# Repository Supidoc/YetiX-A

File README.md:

# YetiX-A

Small development board for the NXP MCX-A series MCUs.

YetiX-A is designed to be compact while still exposing most peripherals needed for firmware development, board bring-up, and protocol testing.

## Features

- SPI EEPROM
- SPI micro SD card slot
- CAN transceiver with optional bus termination
- USB-C connector with ISP button support
- 42 board pins exposing almost all MCU peripherals
- 10-pin ARM Cortex debug connector

## Pin Out

Most MCU pins are routed directly to board pins.

Some signals (for example SPI1 MISO, MOSI, and SCK) are internally connected to onboard peripherals and are still exposed as board pins. Other signals (for example debug pins and chip select lines) are only internally connected and not exposed.

For the exact mapping of MCU pins to board pins, see:

- [assets/PIN_Functions.csv](assets/PIN_Functions.csv)

## Quick Start

1. Power the board via the USB-C receptecal or the 5V Pin
2. Connect a debugger to the 10-pin Cortex debug header, or use ISP mode over USB.
3. Flash a minimal firmware project (for example, a GPIO blink) to verify toolchain and board bring-up.

## Programming And Debug

### SWD/JTAG Debug Header

YetiX-A includes a 10-pin ARM Cortex debug connector for standard MCU debugging workflows.

Recommended usage:

1. Power the board from USB-C or the intended external source.
2. Connect your debug probe to the Cortex header.
3. Use your preferred IDE/debug server to connect and flash.

### USB ISP Mode

The board supports ISP using the USB-C interface.

Typical flow:

1. Hold the ISP button.
2. Connect USB or reset the target if already connected.
3. Release the button.
4. Drag and drop the .uf2 file to the mass storage device.

## Onboard Peripherals

### SPI EEPROM (ST M95256-DF)

- Intended for non-volatile parameter/configuration storage.
- Shares SPI1 bus with SD-card and other externally connected devices.

### SPI micro SD Slot

- Intended for logging, file storage, or data exchange.
- Shares SPI1 bus with EEPROM and other externally connected devices.
- Switch to detect card insertion.

### CAN Transceiver (NXP TJA1042BT)

- 5V CAN Transceiver
- Optional footprints for termination.

## Documentation And Design Files

### KiCad Source

- Schematic: [YetiX-A_DevBoard.kicad_sch](YetiX-A_DevBoard.kicad_sch)
- PCB: [YetiX-A_DevBoard.kicad_pcb](YetiX-A_DevBoard.kicad_pcb)
- Project: [YetiX-A_DevBoard.kicad_pro](YetiX-A_DevBoard.kicad_pro)

### Exported Documentation

- Schematic PDF: [FabData/YetiX-A_Schematic.pdf](FabData/YetiX-A_Schematic.pdf)
- PCB layout PDF: [FabData/YetiX-A_PCB_Layout.pdf](FabData/YetiX-A_PCB_Layout.pdf)

### Manufacturing Outputs

All Documents for fabrication can be found in [FabData](FabData)

## Hardware Revisions

| Revision | Date | Notes |
| --- | --- | --- |
| 0.0.1 | - | Initial production package |
| 0.0.2 | - | Added optional CAN Termination |

## License

See [LICENSE](LICENSE).

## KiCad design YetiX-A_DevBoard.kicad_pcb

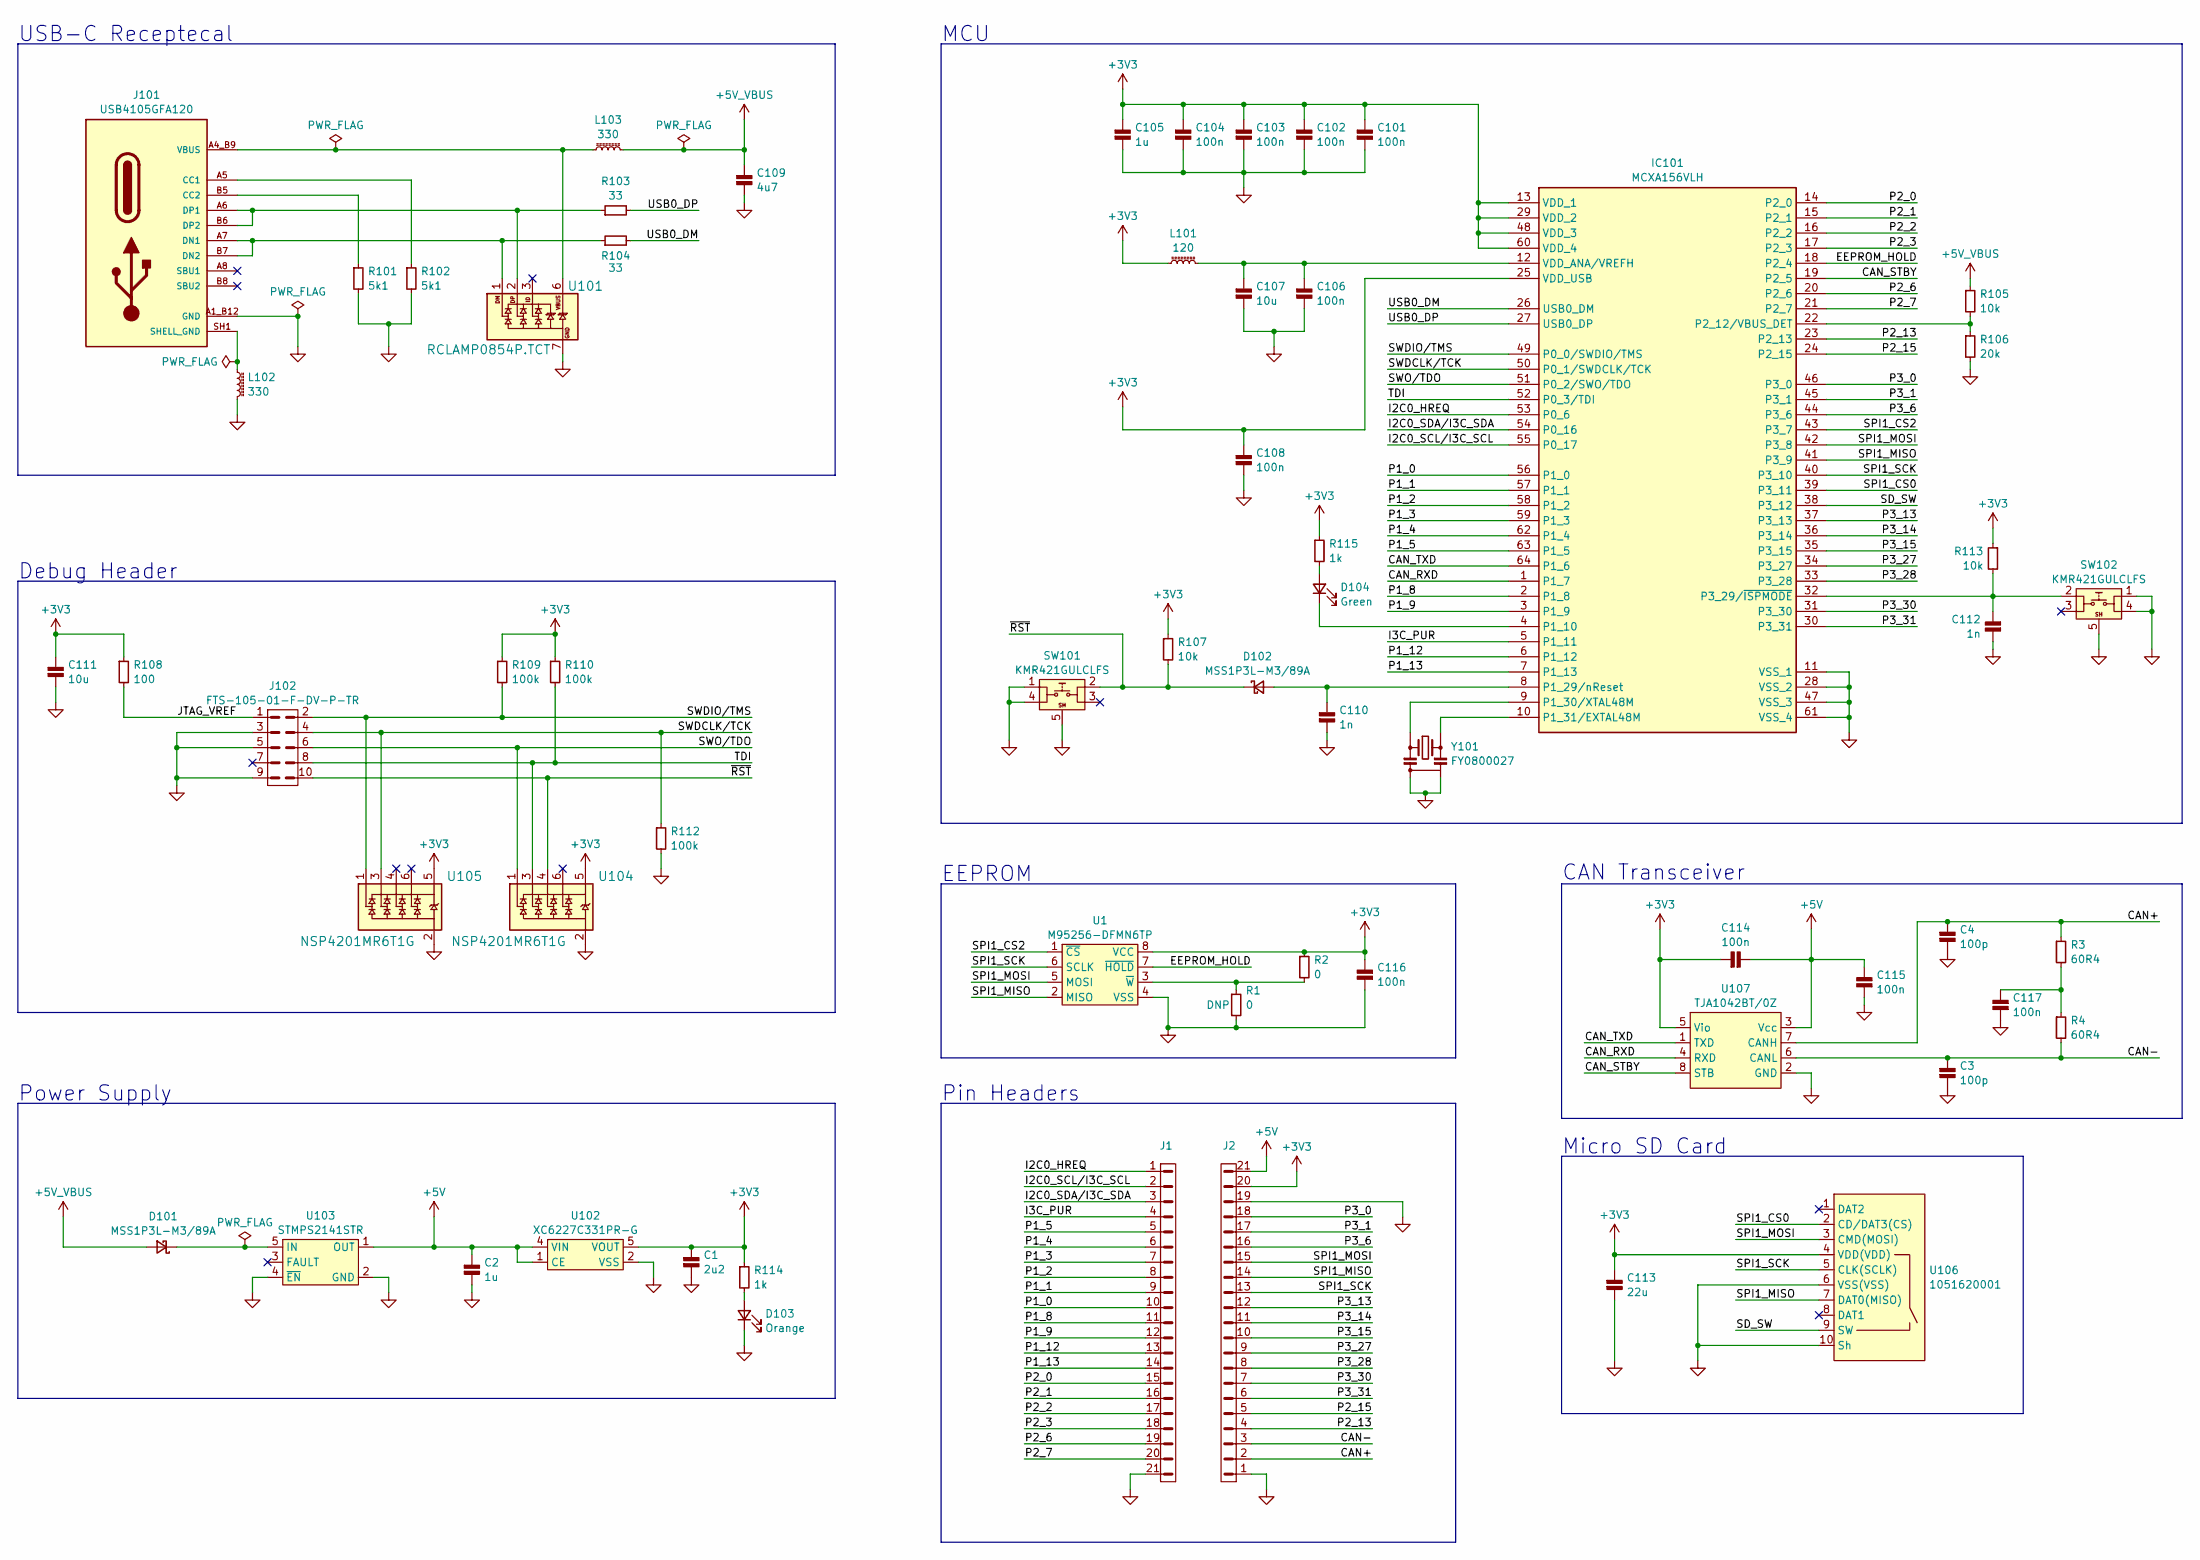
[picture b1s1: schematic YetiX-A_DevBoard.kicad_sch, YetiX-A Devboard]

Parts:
C1: 2u2; C_0603; Rating 10V 20%; MFR# CC0603KRX7R6BB225
C2, C105: 1u; C_0603; Rating 16V 10%; MFR# CC0603KRX7R7BB105
C3, C4: 100p; C_0603; Rating 100V 10%; MFR# CC0603KRX7R0BB101
C101, C102, C103, C104, C106, C108, C114, C115, C116, C117: 100n; C_0603; Rating 16V 10%; MFR# CC0603KRX7R7BB104
C107, C111: 10u; C_0603; Rating 10V 20%; MFR# CC0603MRX5R6BB106
C109: 4u7; C_0603; Rating 16V 10%; MFR# CC0603KRX5R7BB475
C110, C112: 1n; C_0603; Rating 50V 10%; MFR# CC0603KRX7R9BB103
C113: 22u; C_1206; Rating 10V 10%; MFR# CC1206KKX5R6BB226
D101, D102: MSS1P3L-M3/89A; DIODE_MSMP; Rating 30V 1A; MFR# MSS1P3L-M3/89A
D103: Orange; D_0603; Rating 2v 20mA 605nm; MFR# LTST-C190KFKT
D104: Green; D_0603; Rating 2v1 20mA 569nm; MFR# LTST-C190GKT
IC101: MCXA156VLH; QFP50P1200X1200X160-64N; MFR# MCXA156VLH
J1, J2: CONN HEADER VERT 22POS 2.54MM; PinHeader_1x21_P2.54mm_Vertical; MFR# 61302211121
J101: USB4105GFA120; GCT_USB4105GFA120; Rating 16 Pin; MFR# USB4105-GF-A-120
J102: FTS-105-01-F-DV-P-TR; FTS-105-01-X-DV; Rating 1.27 Pitch; MFR# FTS-105-01-F-DV-P-TR
L101: 120; L_0402; Rating 25% 550mA; MFR# BLM15AG121SN1D
L102, L103: 330; L_0603; Rating 330 Ohms @ 100 MHz 1.7A 80mOhm; MFR# MPZ1608S331ATA00
R1: 0; R_0603_DNP
R2: 0; R_0603; Rating 100mW; MFR# RC0603JR-070RL
R3, R4: 60R4; R_0805; Rating 125mW, 1%; MFR# RC0805FR-0760R4L
R101, R102: 5k1; R_0603; Rating 100mW, 1%; MFR# RC0603FR-075K1L
R103, R104: 33; R_0603; Rating 100mW, 1%; MFR# RC0603FR-0733RL
R105, R107, R113: 10k; R_0603; Rating 100mW, 1%; MFR# RC0603FR-0710KL
R106: 20k; R_0603; Rating 100mW, 1%; MFR# RC0603FR-0720KL
R108: 100; R_0603; Rating 100mW, 1%; MFR# RC0603FR-07100RL
R109, R110, R112: 100k; R_0603; Rating 100mW, 1%; MFR# RC0603FR-07100KL
R114, R115: 1k; R_0603; Rating 100mW, 1%; MFR# RC0603FR-071KL
SW101, SW102: KMR421GULCLFS; Rating 1VA; MFR# KMR421GULCLFS
U1: M95256-DFMN6TP; SOIC-8_3.9x4.9mm_P1.27mm; Rating 32kx8b 20MHZ; MFR# M95256-DFMN6TP
U101: RCLAMP0854P.TCT; UFDFN06_1P6X1P6; Rating 5.5VWM 30VC; MFR# RCLAMP0854P.TCT
U102: XC6227C331PR-G; SOT-89-5; Rating 700mA 3v3; MFR# XC6227C331PR-G
U103: STMPS2141STR; SOT-23-5; Rating 500mA; MFR# STMPS2141STR
U104, U105: NSP4201MR6T1G; TSOP-6; Rating 4 Channel 3pF @ 1MHz; MFR# NSP4201MR6T1G
U106: 1051620001; MFR# 1051620001
U107: TJA1042BT/0Z; SOT96-1; Rating 5 mbps; MFR# TJA1042BT/0Z
Y101: FY0800027; Rating 8 MHz ±20ppm; MFR# FY0800027

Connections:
+3V3: C1.1, C101.1, C102.1, C103.1, C104.1, C105.1, C108.1, C111.1, C113.1, C114.1, C116.2, IC101.13 (VDD_1), IC101.25 (VDD_USB), IC101.29 (VDD_2), IC101.48 (VDD_3), IC101.60 (VDD_4), J2.20, L101.1, R2.1, R107.1, R108.1, R109.1, R110.1, R113.1, R114.1, R115.1, U1.8 (VCC), U102.5 (VOUT), U104.5 (Vp), U105.5 (Vp), U106.4 (VDD(VDD)), U107.5 (Vio)
+5V: C2.1, C114.2, C115.2, J2.21, U102.1 (CE), U102.4 (VIN), U103.1 (OUT), U107.3 (Vcc)
+5V_VBUS: C109.1, D101.1 (K), L103.2, R105.1
/CAN+: C4.1, J2.2, R3.1, U107.7 (CANH)
/CAN-: C3.1, J2.3, R4.2, U107.6 (CANL)
/CAN_RXD: IC101.1 (P1_7), U107.4 (RXD)
/CAN_STBY: IC101.19 (P2_5), U107.8 (STB)
/CAN_TXD: IC101.64 (P1_6), U107.1 (TXD)
/EEPROM_HOLD: IC101.18 (P2_4), U1.7 (~HOLD)
/I2C0_HREQ: IC101.53 (P0_6), J1.1
/I2C0_SCL/I3C_SCL: IC101.55 (P0_17), J1.2
/I2C0_SDA/I3C_SDA: IC101.54 (P0_16), J1.3
/I3C_PUR: IC101.5 (P1_11), J1.4
/JTAG_VREF: J102.1, R108.2
/P1_0: IC101.56 (P1_0), J1.10
/P1_1: IC101.57 (P1_1), J1.9
/P1_2: IC101.58 (P1_2), J1.8
/P1_3: IC101.59 (P1_3), J1.7
/P1_4: IC101.62 (P1_4), J1.6
/P1_5: IC101.63 (P1_5), J1.5
/P1_8: IC101.2 (P1_8), J1.11
/P1_9: IC101.3 (P1_9), J1.12
/P1_12: IC101.6 (P1_12), J1.13
/P1_13: IC101.7 (P1_13), J1.14
/P2_0: IC101.14 (P2_0), J1.15
/P2_1: IC101.15 (P2_1), J1.16
/P2_2: IC101.16 (P2_2), J1.17
/P2_3: IC101.17 (P2_3), J1.18
/P2_6: IC101.20 (P2_6), J1.19
/P2_7: IC101.21 (P2_7), J1.20
/P2_13: IC101.23 (P2_13), J2.4
/P2_15: IC101.24 (P2_15), J2.5
/P3_0: IC101.46 (P3_0), J2.18
/P3_1: IC101.45 (P3_1), J2.17
/P3_6: IC101.44 (P3_6), J2.16
/P3_13: IC101.37 (P3_13), J2.12
/P3_14: IC101.36 (P3_14), J2.11
/P3_15: IC101.35 (P3_15), J2.10
/P3_27: IC101.34 (P3_27), J2.9
/P3_28: IC101.33 (P3_28), J2.8
/P3_30: IC101.31 (P3_30), J2.7
/P3_31: IC101.30 (P3_31), J2.6
/SD_SW: IC101.38 (P3_12), U106.9 (SW)
/SPI1_CS0: IC101.39 (P3_11), U106.2 (CD/DAT3(CS))
/SPI1_CS2: IC101.43 (P3_7), U1.1 (~CS)
/SPI1_MISO: IC101.41 (P3_9), J2.14, U1.2 (MISO), U106.7 (DAT0(MISO))
/SPI1_MOSI: IC101.42 (P3_8), J2.15, U1.5 (MOSI), U106.3 (CMD(MOSI))
/SPI1_SCK: IC101.40 (P3_10), J2.13, U1.6 (SCLK), U106.5 (CLK(SCLK))
/SWDCLK/TCK: IC101.50 (P0_1/SWDCLK/TCK), J102.4, R112.1, U105.3 (I/O)
/SWDIO/TMS: IC101.49 (P0_0/SWDIO/TMS), J102.2, R109.2, U105.1 (I/O)
/SWO/TDO: IC101.51 (P0_2/SWO/TDO), J102.6, U104.1 (I/O)
/TDI: IC101.52 (P0_3/TDI), J102.8, R110.2, U104.3 (I/O)
/USB0_DM: IC101.26 (USB0_DM), R104.2
/USB0_DP: IC101.27 (USB0_DP), R103.2
/~RST: D102.2 (K), J102.10, R107.2, SW101.2, U104.4 (I/O)
GND: C1.2, C2.2, C3.2, C4.2, C101.2, C102.2, C103.2, C104.2, C105.2, C106.2, C107.2, C108.2, C109.2, C110.2, C111.2, C112.2, C113.2, C115.1, C116.1, C117.1, D103.2 (K), IC101.11 (VSS_1), IC101.28 (VSS_2), IC101.47 (VSS_3), IC101.61 (VSS_4), J1.21, J2.1, J2.19, J101.A1_B12 (GND), J101.B1_A12 (GND), J102.3, J102.5, J102.9, L102.2, R1.2, R101.2, R102.2, R106.2, R112.2, SW101.1, SW101.4 (3), SW101.5 (SH), SW102.1, SW102.4 (3), SW102.5 (SH), U1.4 (VSS), U101.7 (GND), U102.2 (VSS), U103.2 (GND), U103.4 (~EN), U104.2 (Vn), U105.2 (Vn), U106.6 (VSS(VSS)), U106.10 (Sh), U106.11 (Sh), U106.12 (Sh), U106.13 (Sh), U106.14 (Sh), U106.15 (Sh), U107.2 (GND), Y101.2 (GND), Y101.4 (GND)
unnamed: C117.2, R3.2, R4.1
unnamed: D103.1 (A), R114.2
unnamed: D104.1 (A), R115.2
unnamed: D104.2 (K), IC101.4 (P1_10)
unnamed: C110.1, D102.1 (K), IC101.8 (P1_29/nReset)
unnamed: IC101.9 (P1_30/XTAL48M), Y101.1 (Crystal_1)
unnamed: IC101.10 (P1_31/EXTAL48M), Y101.3 (Crystal_1)
unnamed: IC101.22 (P2_12/VBUS_DET), R105.2, R106.1
unnamed: C112.1, IC101.32 (P3_29/~ISPMODE), R113.2, SW102.2
unnamed: C106.1, C107.1, IC101.12 (VDD_ANA/VREFH), L101.2
unnamed: J101.A5 (CC1), R102.1
unnamed: J101.B5 (CC2), R101.1
unnamed: J101.A7 (DN1), J101.B7 (DN2), R104.1, U101.1 (DM)
unnamed: J101.A6 (DP1), J101.B6 (DP2), R103.1, U101.2 (DP)
unnamed: R1.1, R2.2, U1.3 (~W)
unnamed: D101.2 (K), U103.5 (IN)
SHELL_GND: J101.SH1 (SHELL_GND), J101.SH2 (SHELL_GND), J101.SH3 (SHELL_GND), J101.SH4 (SHELL_GND), L102.1
VBUS: J101.A4_B9 (VBUS), J101.B4_A9 (VBUS), L103.1, U101.6 (VBUS)

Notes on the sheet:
MCU
Pin Headers
USB-C Receptecal
Micro SD Card
Debug Header
Power Supply
CAN Transceiver
EEPROM

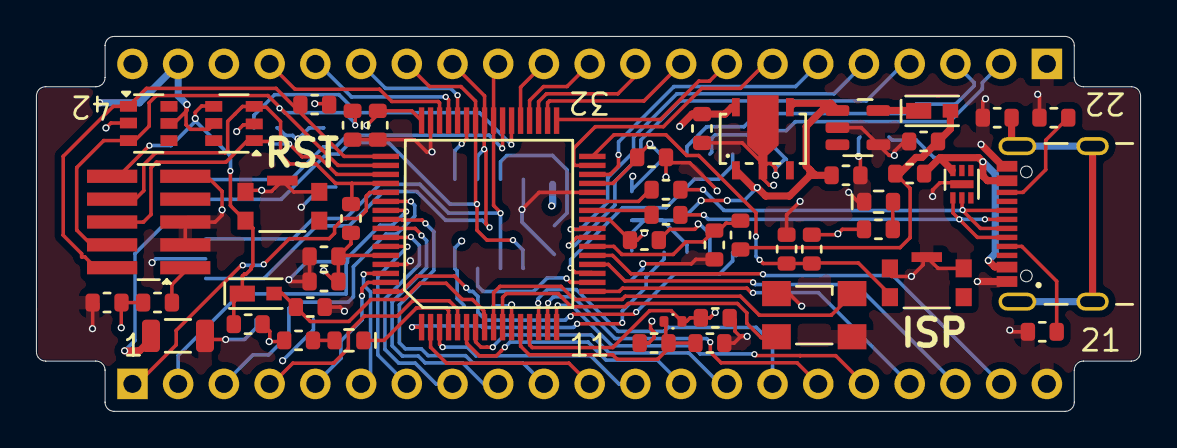
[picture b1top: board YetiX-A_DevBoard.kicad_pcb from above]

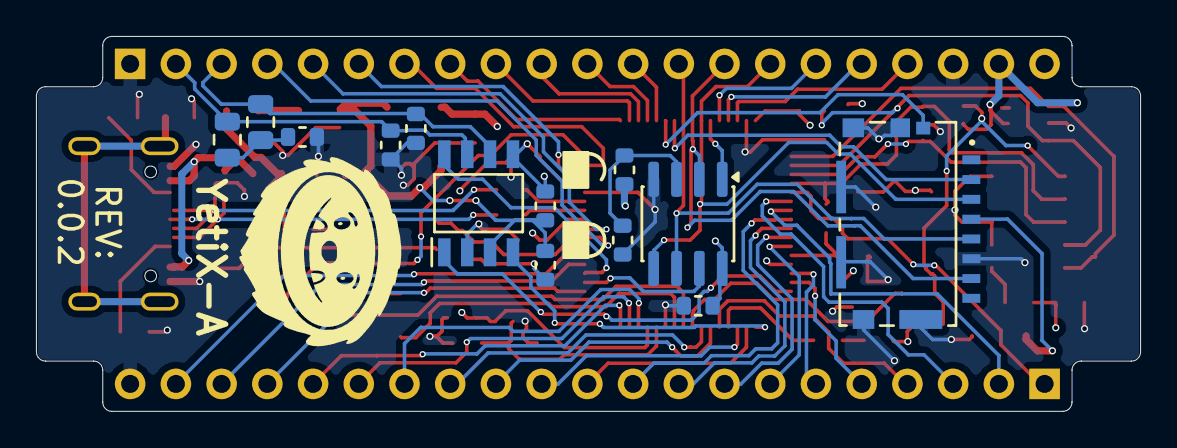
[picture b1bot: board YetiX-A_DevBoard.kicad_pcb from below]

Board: 4 copper layers, 61.3 x 20.8 mm, 62 parts (15 on the bottom side), 74 nets.

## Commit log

2026-03-31 Rev: 0.0.1
2026-04-01 Rev: 0.0.2
    - Added filtering capacitors on CAN output.
    - Added optional CAN termination
2026-04-07 QR-Code
    - Added QR-Code with link to github repository
2026-04-07 Pin FUnctions Table Update
2026-04-07 Initial README
